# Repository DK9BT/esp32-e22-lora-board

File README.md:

# ESP32-E22-LoRa-board
Carrier Board for LoRa Tranceiver like E22-400M33S and ESP32 MCU

### Main Parts List:

EBYTE E22-400M33S (2W/33dBm) https://www.amazon.de/dp/B0BMP99S3D

if needed: E22->N Pigtail: https://www.amazon.de/dp/B0C8J131PD

ESP32 Board Dev Kit C V4 https://www.amazon.de/dp/B08BTS62L7/ / https://www.amazon.de/dp/B07Z83MF5W/

Adapter-Kabel zum flashen im eingebauten Zustand https://www.amazon.de/dp/B096843RY3/

BME/BMP280 3,3V https://www.amazon.de/dp/B07FS95JXT/

OLED-Display (VCC-GND-SCL-SDA): https://www.amazon.de/dp/B0C9LJ898Z/

GPS https://www.amazon.de/dp/B0D3DJ58R8/

Reichelt: https://www.reichelt.de/my/2192127

### Versions Info
**V 2.1.2  PCB** für Querformat im Gehäuse für Aussenmontage - alle Anschlüsse auf der Unterseite des Gehäuses  
oder PCB vertikale Einbau

___

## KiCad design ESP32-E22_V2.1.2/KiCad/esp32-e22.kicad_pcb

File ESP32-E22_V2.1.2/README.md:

# ESP32-E22-LoRa-board V2.1.2 - FINAL
• Carrier Board for Lora Tranceiver like E22-400M33S and ESP32 MCU  

siehe 

___
***OE3WAS - Wolfgang - 4.2.2025***

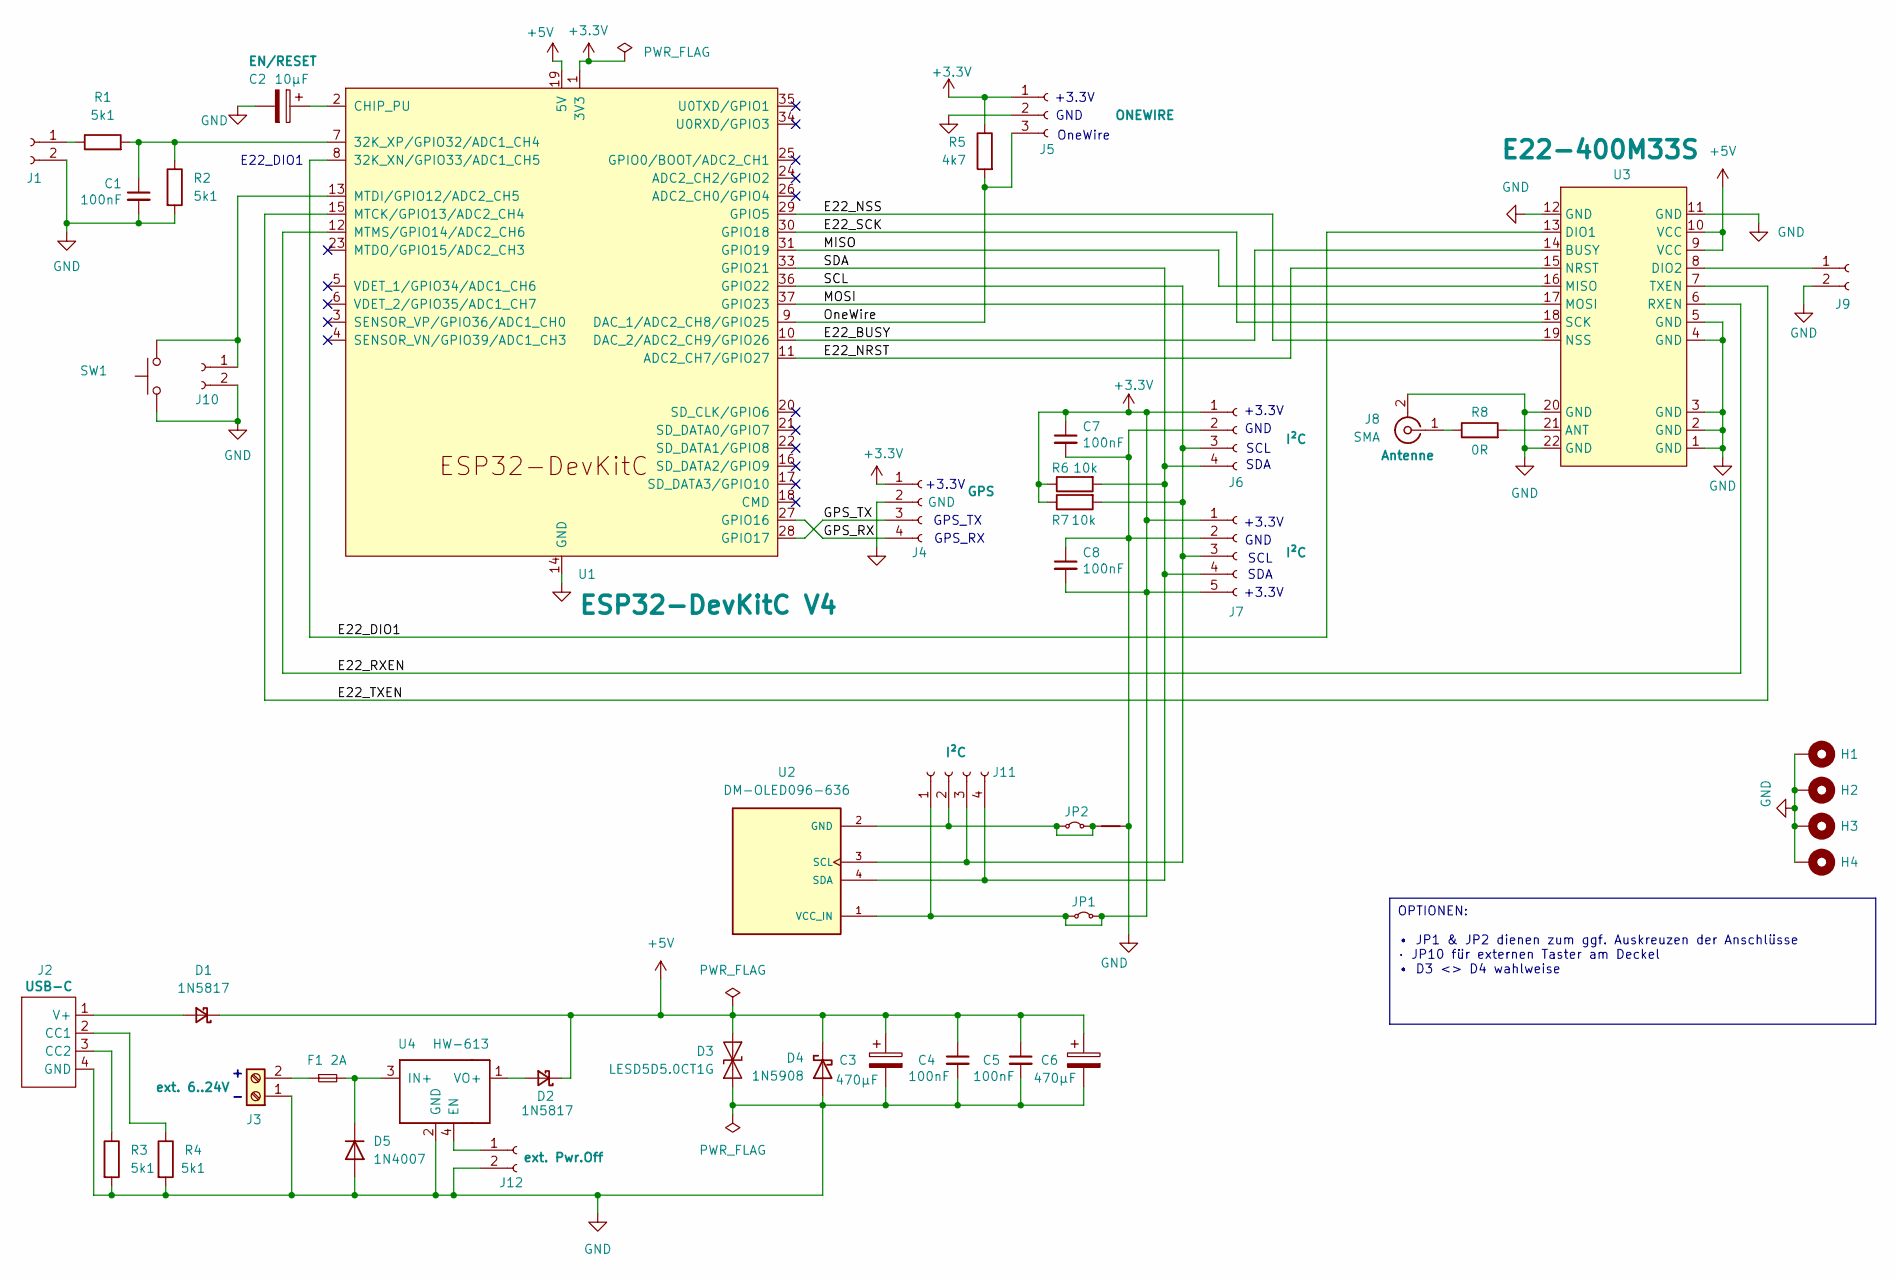
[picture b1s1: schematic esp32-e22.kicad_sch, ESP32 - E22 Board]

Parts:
C1, C4, C5, C7, C8: 100nF; C_Disc_D4.7mm_W2.5mm_P5.00mm
C2: 10µF; CP_Radial_D6.3mm_P2.50mm
C3, C6: 470µF; CP_Radial_D5.0mm_P2.50mm
D1: 1N5817; D_DO-41_SOD81_P5.08mm_Vertical_KathodeUp
D2: 1N5817; D_DO-41_SOD81_P7.62mm_Horizontal
D3: LESD5D5.0CT1G; D_SOD-523
D4: 1N5908; D_DO-201_P12.70mm_Horizontal
D5: 1N4007; D_DO-41_SOD81_P2.54mm_Vertical_KathodeUp
F1: 2A; R_Axial_DIN0411_L9.9mm_D3.6mm_P5.08mm_Vertical
H1, H2, H3, H4: MountingHole_Pad; MountingHole_2.2mm_M2_Pad_TopBottom
J1, J9, J10: Conn_01x02_Socket; PinHeader_1x02_P2.54mm_Vertical
J2: USB-C_vert
J3: Screw_Terminal_01x02; TerminalBlock_Phoenix_MKDS-1,5-2-5.08_1x02_P5.08mm_Horizont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
J4: Conn_01x04_Socket; PinHeader_1x04_P2.54mm_Vertical
J5: Conn_01x03_Socket; PinHeader_1x03_P2.54mm_Vertical
J6, J11: Conn_01x04_Socket; PinSocket_1x04_P2.54mm_Vertical
J7: Conn_01x05_Socket; PinSocket_1x05_P2.54mm_Vertical
J8: SMA; SMA_Amphenol_901-143_Horizontal
J12: Conn_01x02_Socket; PinHeader_1x02_P2.54mm_Horizontal
JP1, JP2: Jumper_2_Small_Bridged; TestPoint_2Pads_Pitch2.54mm_Drill0.8mm
NT1: NetTie_2; NetTie-2_SMD_Pad0.5mm
R1, R2, R3, R4: 5k1; R_Axial_DIN0207_L6.3mm_D2.5mm_P7.62mm_Horizontal
R5: 4k7; R_Axial_DIN0207_L6.3mm_D2.5mm_P7.62mm_Horizontal
R6, R7: 10k; R_Axial_DIN0207_L6.3mm_D2.5mm_P7.62mm_Horizontal
R8: 0R; R_0805_2012Metric
SW1: SW_Push; SW_PUSH_6mm
U1: ESP32-DevKitC V4; ESP32-DevKitC
U2: DM-OLED096-636; PARTREV 2018-09-10
U3: E22-400M33S
U4: HW-613

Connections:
+3.3V: C7.1, C8.2, J4.1, J5.1, J6.1, J7.1, J7.5, J11.1, JP1.1 (A), JP1.2 (B), R5.1, R6.1, R7.1, U1.1 (3V3), U2.1 (VCC_IN)
+5V: C3.1, C4.1, C5.1, C6.1, D1.1 (K), D2.1 (K), D3.1 (A1), D4.1 (K), U1.19 (5V), U3.9 (VCC), U3.10 (VCC)
/E22_BUSY: U1.10 (DAC_2/ADC2_CH9/GPIO26), U3.14 (BUSY)
/E22_DIO1: U1.8 (32K_XN/GPIO33/ADC1_CH5), U3.13 (DIO1)
/E22_NRST: U1.11 (ADC2_CH7/GPIO27), U3.15 (NRST)
/E22_NSS: U1.29 (GPIO5), U3.19 (NSS)
/E22_RXEN: U1.12 (MTMS/GPIO14/ADC2_CH6), U3.6 (RXEN)
/E22_SCK: U1.30 (GPIO18), U3.18 (SCK)
/E22_TXEN: U1.15 (MTCK/GPIO13/ADC2_CH4), U3.7 (TXEN)
/GPS_RX: J4.4, U1.27 (GPIO16)
/GPS_TX: J4.3, U1.28 (GPIO17)
/MISO: U1.31 (GPIO19), U3.16 (MISO)
/MOSI: U1.37 (GPIO23), U3.17 (MOSI)
/OneWire: J5.3, R5.2, U1.9 (DAC_1/ADC2_CH8/GPIO25)
/SCL: J6.3, J7.3, J11.3, R7.2, U1.36 (GPIO22), U2.3 (SCL)
/SDA: J6.4, J7.4, J11.4, R6.2, U1.33 (GPIO21), U2.4 (SDA)
GND: C1.2, C2.2, C3.2, C4.2, C5.2, C6.2, C7.2, C8.1, D3.2 (A2), D4.2 (A), D5.2 (A), H1.1, H2.1, H3.1, H4.1, J1.2, J2.4 (GND), J3.1, J4.2, J5.2, J6.2, J7.2, J8.2 (Ext), J9.2, J10.2, J12.2, NT1.2, R2.2, R3.2, R4.2, SW1.1, U1.14 (GND), U1.32 (GND), U1.38 (GND), U3.1 (GND), U3.2 (GND), U3.3 (GND), U3.4 (GND), U3.5 (GND), U3.11 (GND), U3.12 (GND), U3.20 (GND), U3.22 (GND), U4.2 (GND)
unnamed: D1.2 (A), J2.1 (V+)
unnamed: D2.2 (A), U4.1 (VO+)
unnamed: D5.1 (K), F1.2, U4.3 (IN+)
unnamed: J1.1, R1.1
unnamed: J2.2 (CC1), R4.1
unnamed: J2.3 (CC2), R3.1
unnamed: F1.1, J3.2
unnamed: J8.1 (In), R8.1
unnamed: J9.1, U3.8 (DIO2)
unnamed: J10.1, SW1.2, U1.13 (MTDI/GPIO12/ADC2_CH5)
unnamed: J11.2, JP2.1 (A), JP2.2 (B), NT1.1, U2.2 (GND)
unnamed: J12.1, U4.4 (EN)
unnamed: C1.1, R1.2, R2.1, U1.7 (32K_XP/GPIO32/ADC1_CH4)
unnamed: C2.1, U1.2 (CHIP_PU)
unnamed: R8.2, U3.21 (ANT)

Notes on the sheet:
OPTIONEN: • JP1 & JP2 dienen zum ggf. Auskreuzen der Anschlüsse · JP10 für externen Taster am Deckel • D3 <> D4 wahlweise
GND
SCL
+3.3V
GPS_TX
OneWire
SDA
GPS_RX
E22_DIO1

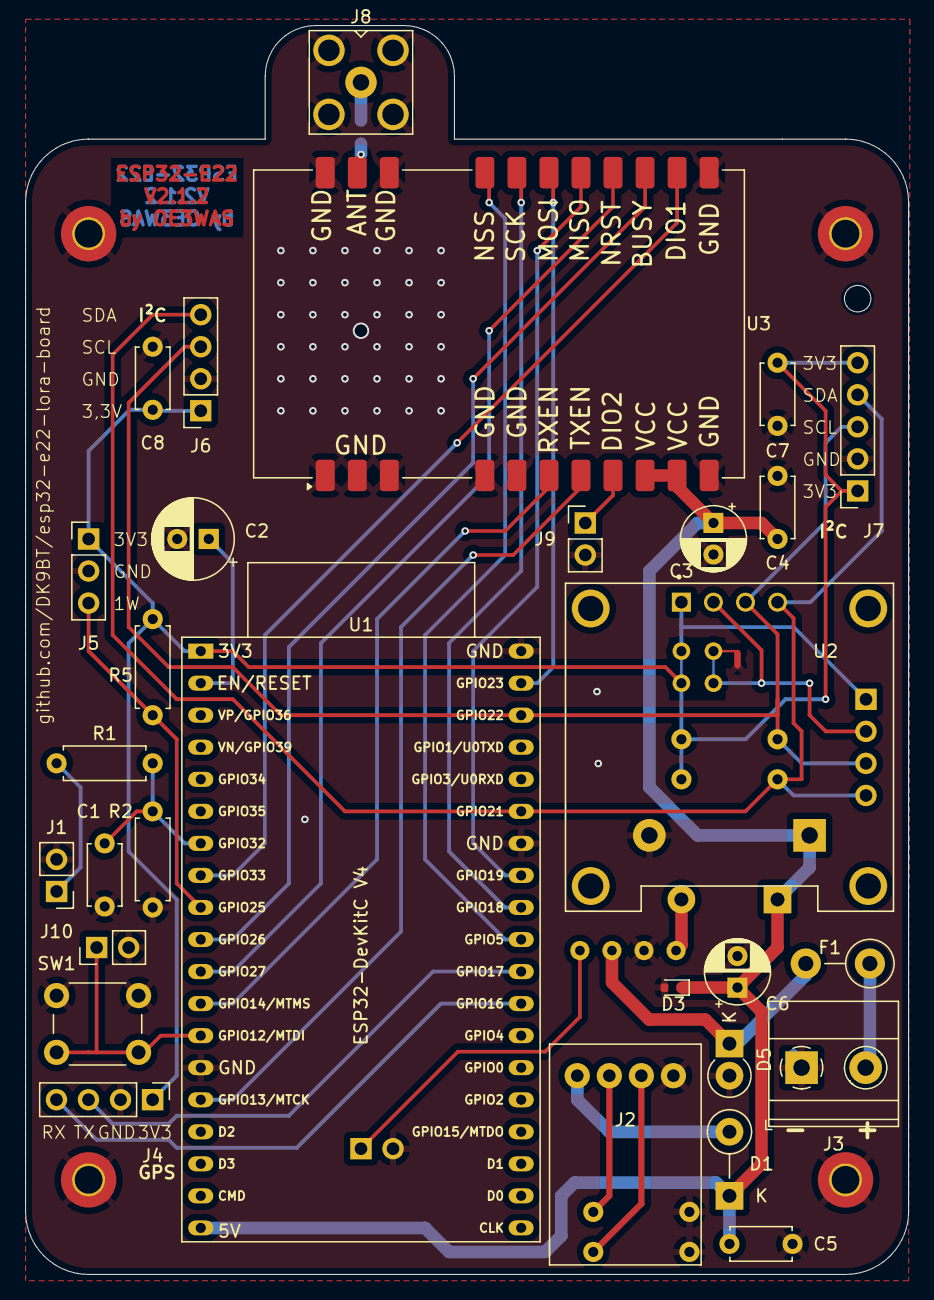
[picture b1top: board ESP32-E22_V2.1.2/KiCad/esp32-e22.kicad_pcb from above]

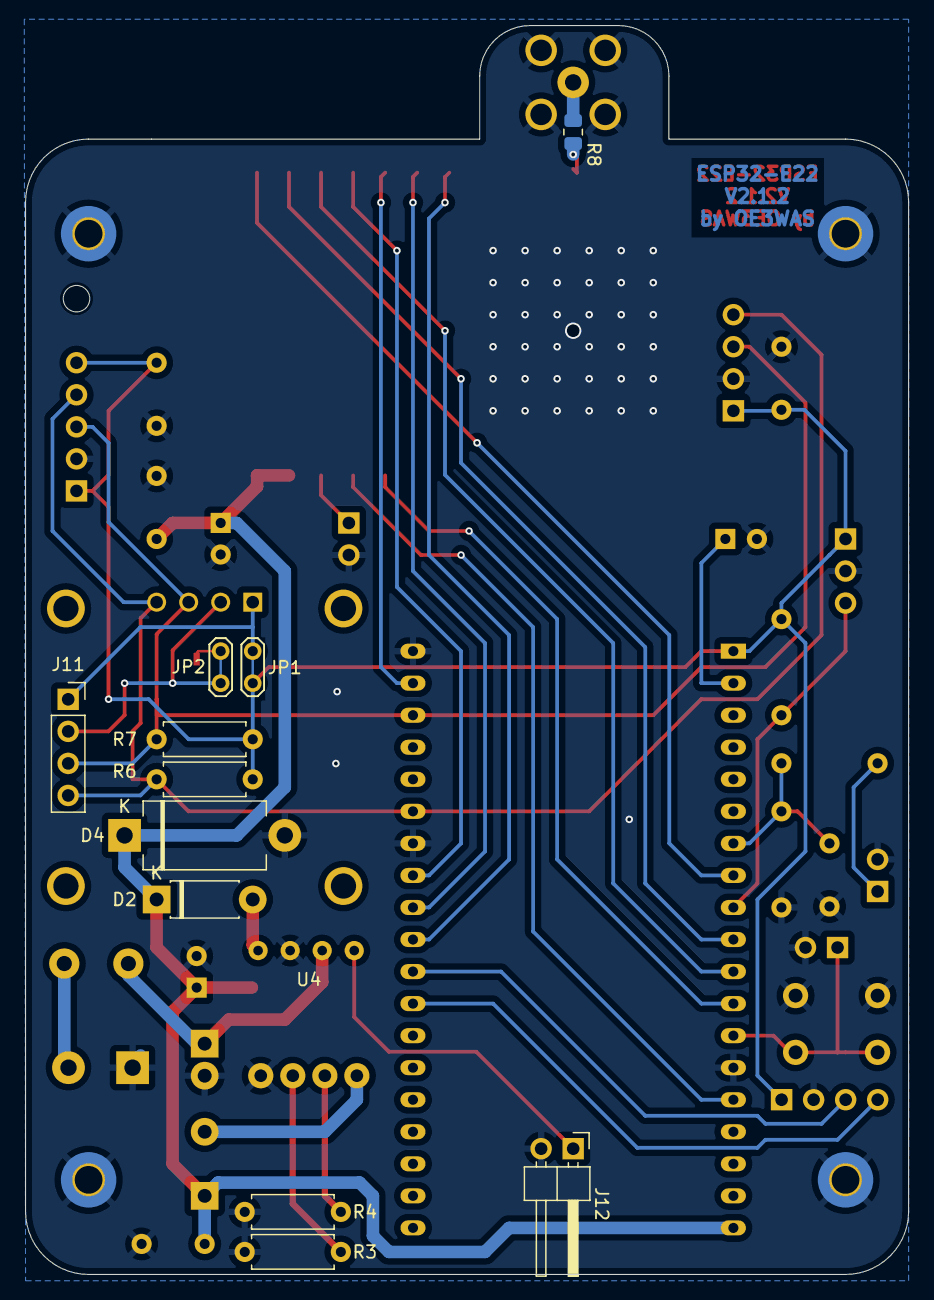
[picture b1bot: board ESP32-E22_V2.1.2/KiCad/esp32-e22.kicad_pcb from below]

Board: 2 copper layers, 70.0 x 99.0 mm, 46 parts (12 on the bottom side), 32 nets.

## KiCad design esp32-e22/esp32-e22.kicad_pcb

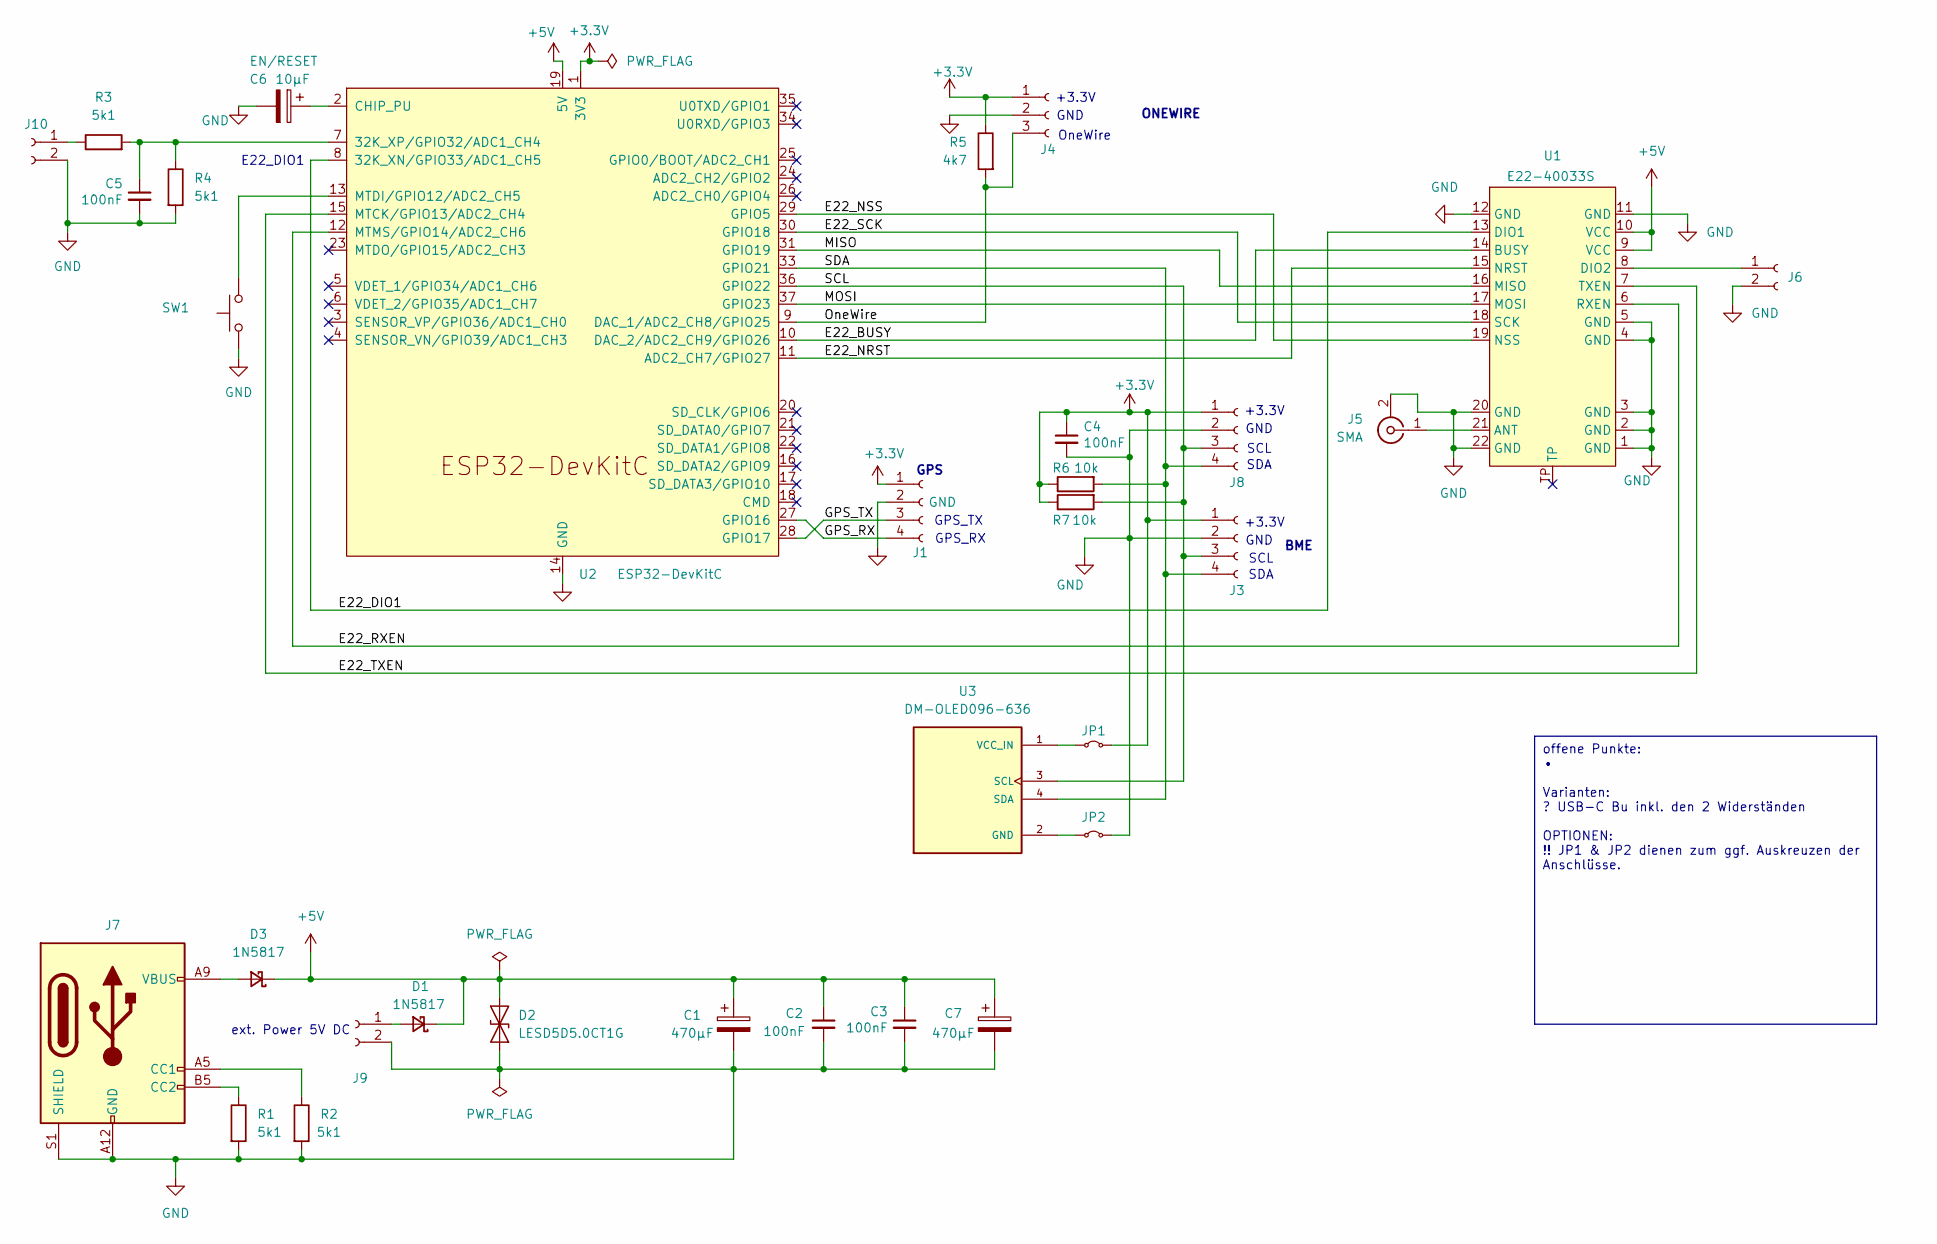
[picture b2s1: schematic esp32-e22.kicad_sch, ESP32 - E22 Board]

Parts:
C1, C7: 470µF; CP_Radial_D5.0mm_P2.50mm
C2, C3, C4, C5: 100nF; C_Disc_D4.7mm_W2.5mm_P5.00mm
C6: 10µF; CP_Radial_D6.3mm_P2.50mm
D1, D3: 1N5817; D_DO-41_SOD81_P7.62mm_Horizontal
D2: LESD5D5.0CT1G; D_SOD-523
J1, J3, J8: Conn_01x04_Socket; PinHeader_1x04_P2.54mm_Vertical
J4: Conn_01x03_Socket; PinHeader_1x03_P2.54mm_Vertical
J5: SMA; SMA_Amphenol_132134-14_Vertical
J6, J10: Conn_01x02_Socket; PinHeader_1x02_P2.54mm_Vertical
J7: USB_C_Receptacle_PowerOnly_6P; USB_C_Receptacle_GCT_USB4125-xx-x-0190_6P_TopMnt_Horizontal
J9: Conn_01x02_Socket; TerminalBlock_Phoenix_MKDS-1,5-2-5.08_1x02_P5.08mm_Horizont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
JP1, JP2: Jumper_2_Small_Bridged; TestPoint_2Pads_Pitch2.54mm_Drill0.8mm
R1, R2, R3, R4: 5k1; R_Axial_DIN0207_L6.3mm_D2.5mm_P7.62mm_Horizontal
R5: 4k7; R_Axial_DIN0207_L6.3mm_D2.5mm_P7.62mm_Horizontal
R6, R7: 10k; R_Axial_DIN0207_L6.3mm_D2.5mm_P7.62mm_Horizontal
SW1: SW_Push; SW_PUSH_6mm
U1: E22-40033S; E22-400M33S
U2: ESP32-DevKitC
U3: DM-OLED096-636; PARTREV 2018-09-10

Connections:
+3.3V: C4.1, J1.1, J3.1, J4.1, J8.1, JP1.2 (B), R5.1, R6.1, R7.1, U2.1 (3V3)
+5V: C1.1, C2.1, C3.1, C7.1, D1.1 (K), D2.2 (A2), D3.1 (K), U1.9 (VCC), U1.10 (VCC), U2.19 (5V)
/E22_BUSY: U1.14 (BUSY), U2.10 (DAC_2/ADC2_CH9/GPIO26)
/E22_DIO1: U1.13 (DIO1), U2.8 (32K_XN/GPIO33/ADC1_CH5)
/E22_NRST: U1.15 (NRST), U2.11 (ADC2_CH7/GPIO27)
/E22_NSS: U1.19 (NSS), U2.29 (GPIO5)
/E22_RXEN: U1.6 (RXEN), U2.12 (MTMS/GPIO14/ADC2_CH6)
/E22_SCK: U1.18 (SCK), U2.30 (GPIO18)
/E22_TXEN: U1.7 (TXEN), U2.15 (MTCK/GPIO13/ADC2_CH4)
/GPS_RX: J1.4, U2.27 (GPIO16)
/GPS_TX: J1.3, U2.28 (GPIO17)
/MISO: U1.16 (MISO), U2.31 (GPIO19)
/MOSI: U1.17 (MOSI), U2.37 (GPIO23)
/OneWire: J4.3, R5.2, U2.9 (DAC_1/ADC2_CH8/GPIO25)
/SCL: J3.3, J8.3, R7.2, U2.36 (GPIO22), U3.3 (SCL)
/SDA: J3.4, J8.4, R6.2, U2.33 (GPIO21), U3.4 (SDA)
GND: C1.2, C2.2, C3.2, C4.2, C5.2, C6.2, C7.2, D2.1 (A1), J1.2, J3.2, J4.2, J5.2 (Ext), J6.2, J7.A12 (GND), J7.B12 (GND), J7.S1 (SHIELD), J8.2, J9.2, J10.2, JP2.2 (B), R1.2, R2.2, R4.2, SW1.1, U1.1 (GND), U1.2 (GND), U1.3 (GND), U1.4 (GND), U1.5 (GND), U1.11 (GND), U1.12 (GND), U1.20 (GND), U1.22 (GND), U2.14 (GND), U2.32 (GND), U2.38 (GND)
unnamed: D1.2 (A), J9.1
unnamed: D3.2 (A), J7.A9 (VBUS), J7.B9 (VBUS)
unnamed: J5.1 (In), U1.21 (ANT)
unnamed: J6.1, U1.8 (DIO2)
unnamed: J7.A5 (CC1), R2.1
unnamed: J7.B5 (CC2), R1.1
unnamed: J10.1, R3.1
unnamed: JP1.1 (A), U3.1 (VCC_IN)
unnamed: JP2.1 (A), U3.2 (GND)
unnamed: C5.1, R3.2, R4.1, U2.7 (32K_XP/GPIO32/ADC1_CH4)
unnamed: C6.1, U2.2 (CHIP_PU)
unnamed: SW1.2, U2.13 (MTDI/GPIO12/ADC2_CH5)

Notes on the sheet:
offene Punkte: • Varianten: ? USB-C Bu inkl. den 2 Widerständen OPTIONEN: !! JP1 & JP2 dienen zum ggf. Auskreuzen der Anschlüsse.
GND
ONEWIRE
SCL
ext. Power 5V DC
BME
GPS
GPS_TX
OneWire
SDA
+3.3V
GPS_RX
E22_DIO1

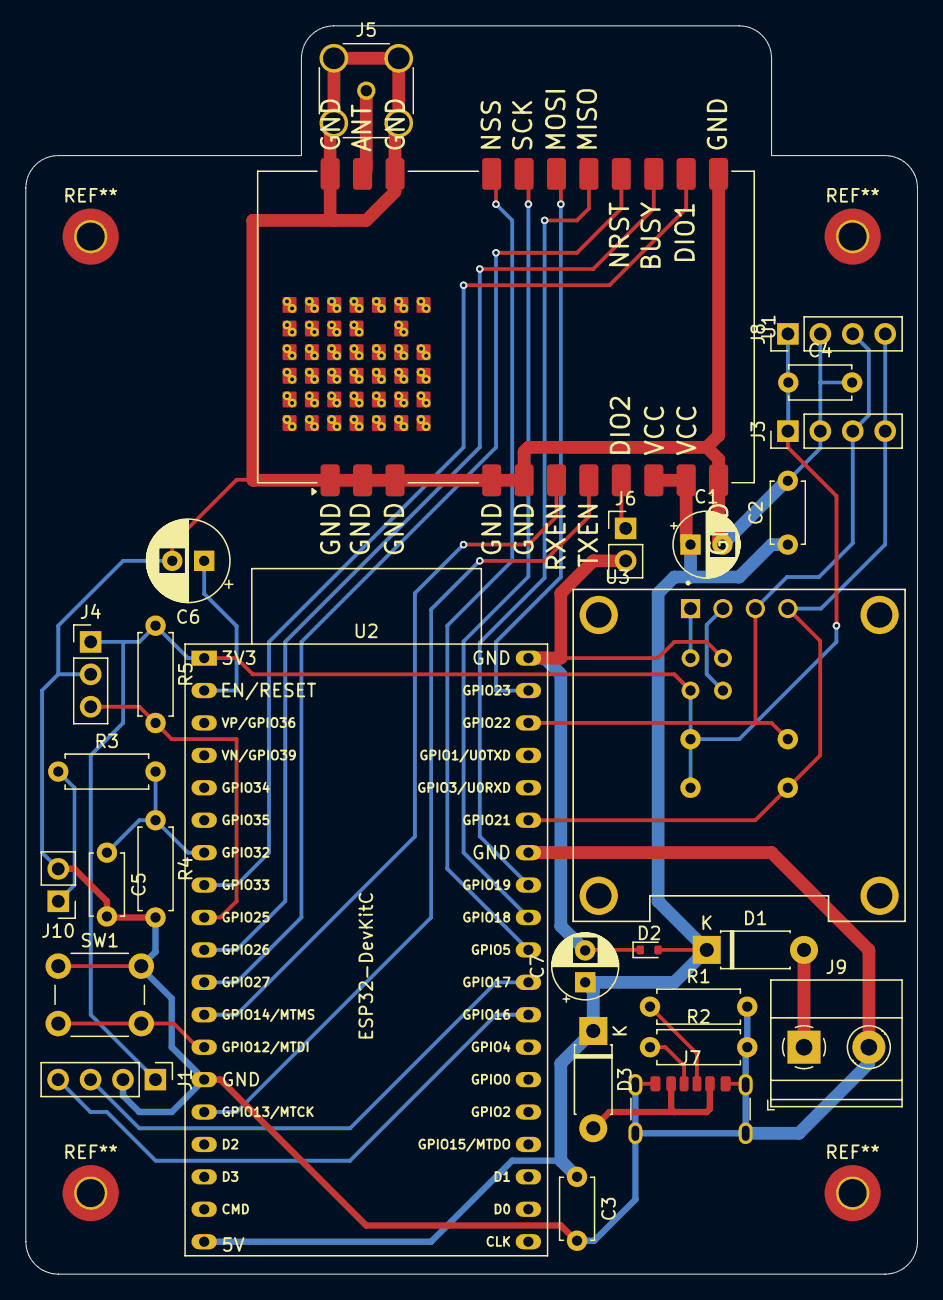
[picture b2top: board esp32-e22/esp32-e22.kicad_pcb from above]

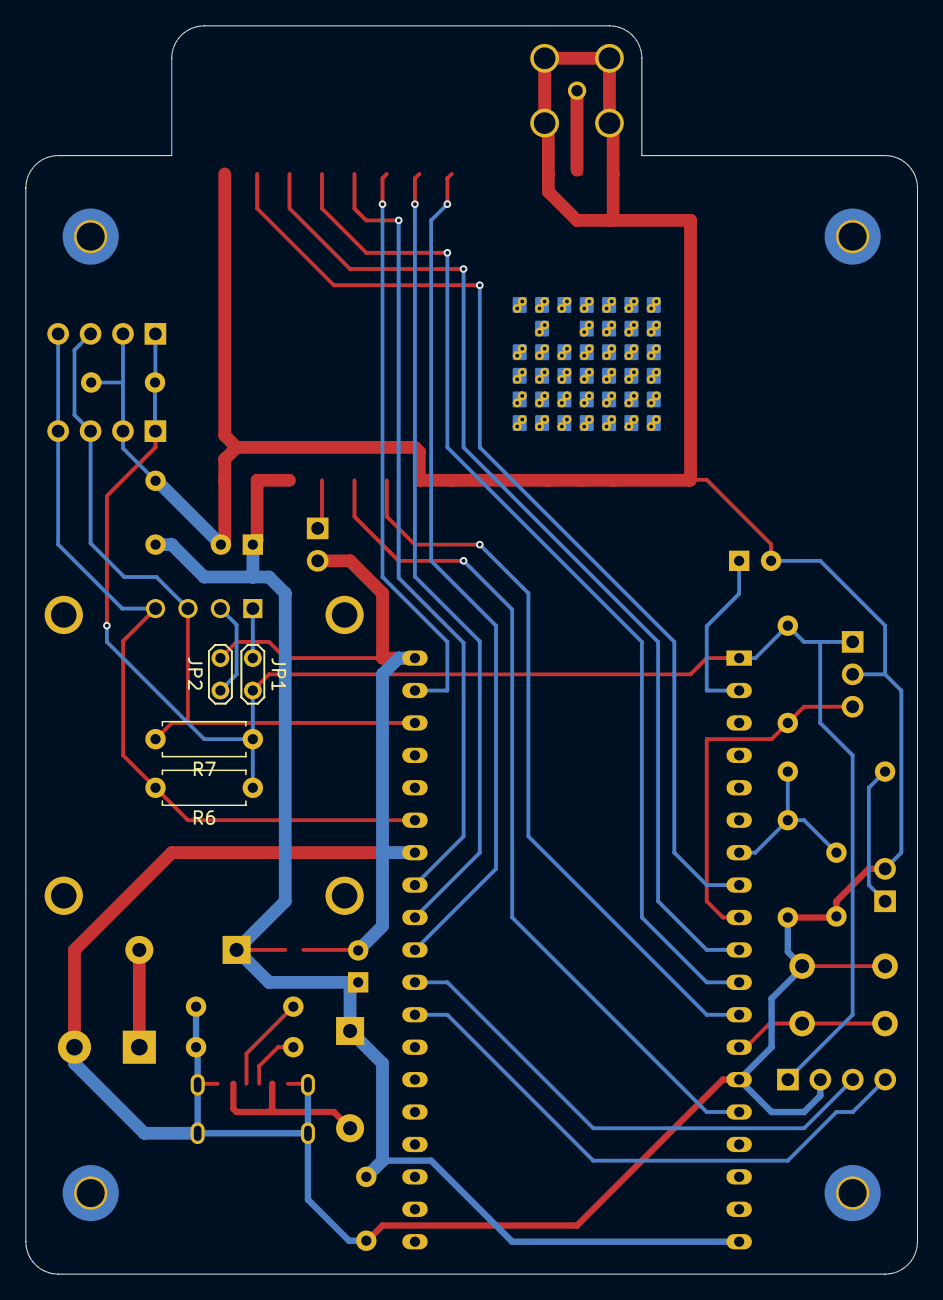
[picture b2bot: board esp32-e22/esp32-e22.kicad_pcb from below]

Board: 2 copper layers, 69.9 x 97.8 mm, 32 parts (4 on the bottom side), 29 nets.

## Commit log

2024-10-03 add usb-c connector
2024-10-03 added schematic and pictures from oe5hwn board
2024-10-04 added schematic pdf of V2.0.3
2024-10-04 update to V2.0.4 (fixed ERC Fails in schematic)
2024-10-04 fixed some missing footprints -> V2.0.5
2024-10-04 Create x
2024-10-04 Rename esp32_devkitc_v4-sch.pdf to Doku/esp32_devkitc_v4-sch.pdf
2024-10-06 Create README.md
    1st creation
2024-10-06 Update README.md
    Links added
2024-10-06 Update README.md
    added
2024-10-07 update footprint of sma connector
2024-10-09 move to folder ESP32-E22_V2.1.x
2024-10-09 move to KiCad subfolder
2024-10-09 rename folder
2024-10-09 rename
2024-10-09 update files
2024-10-09 update ...
2024-10-09 new Version 2.0.10 & 2.0.6
2024-10-10 new Version
2024-10-10 update pictures
2024-10-10 Update README.md - Beta Version
2024-10-11 real update
2024-10-11 cleaning
2024-10-11 backup folder not needed
2024-10-11 Flood filled GND Back and Front
2024-10-11 some footprint changes
2024-10-11 corrected footprints symbols and 3d Models for our custom parts
2024-10-11 some fixes
2024-10-11 Beta V2.1.0
2024-10-11 small fix
2024-10-11 version update SCH
2024-10-13 stückliste
2024-10-13 update BOM
2024-10-15 updated Version
2024-10-17 new V 2.1.1
2024-10-17 update datasheets
2024-10-20 update to V2.1.1-α2
2024-10-24 mask update
2024-10-24 PCB V2.1.1-α3
2024-10-25 SCH & PCB α5
2024-10-25 update SCH
2024-10-30 update PCB
2024-10-31 new pictures
2024-10-31 (c) in Bildern ergänzt
2024-11-02 Update README.md - beta Status
2024-11-02 update PCB V2.1.1 BETA
2024-11-03 update Doku
2024-11-05 new Version 2.1.2
2024-11-05 update Assembly
2024-11-05 update intheBox
2024-11-14 add assembly
2024-11-14 change name
2024-11-15 new pics
2024-11-16 add pics
2024-11-17 PCB β3
2024-11-17 add pic
2024-11-17 new pic
2024-11-21 app pics
2024-11-22 final
2024-11-22 add jlcpb gerber production files
2024-11-23 cleanup
2024-11-28 add Bestückungspläne
2025-02-04 archive old
2025-02-04 archive
2025-03-04 add data
2025-11-24 Fix typo in GPS section of README.md
2025-11-24 Enhance README with GPS module details and images
    Updated GPS module installation instructions and added images.
2025-11-24 Revise README with new copyright and module details
    Updated copyright date and added additional information about the INA226 module and BME280 sensor.
